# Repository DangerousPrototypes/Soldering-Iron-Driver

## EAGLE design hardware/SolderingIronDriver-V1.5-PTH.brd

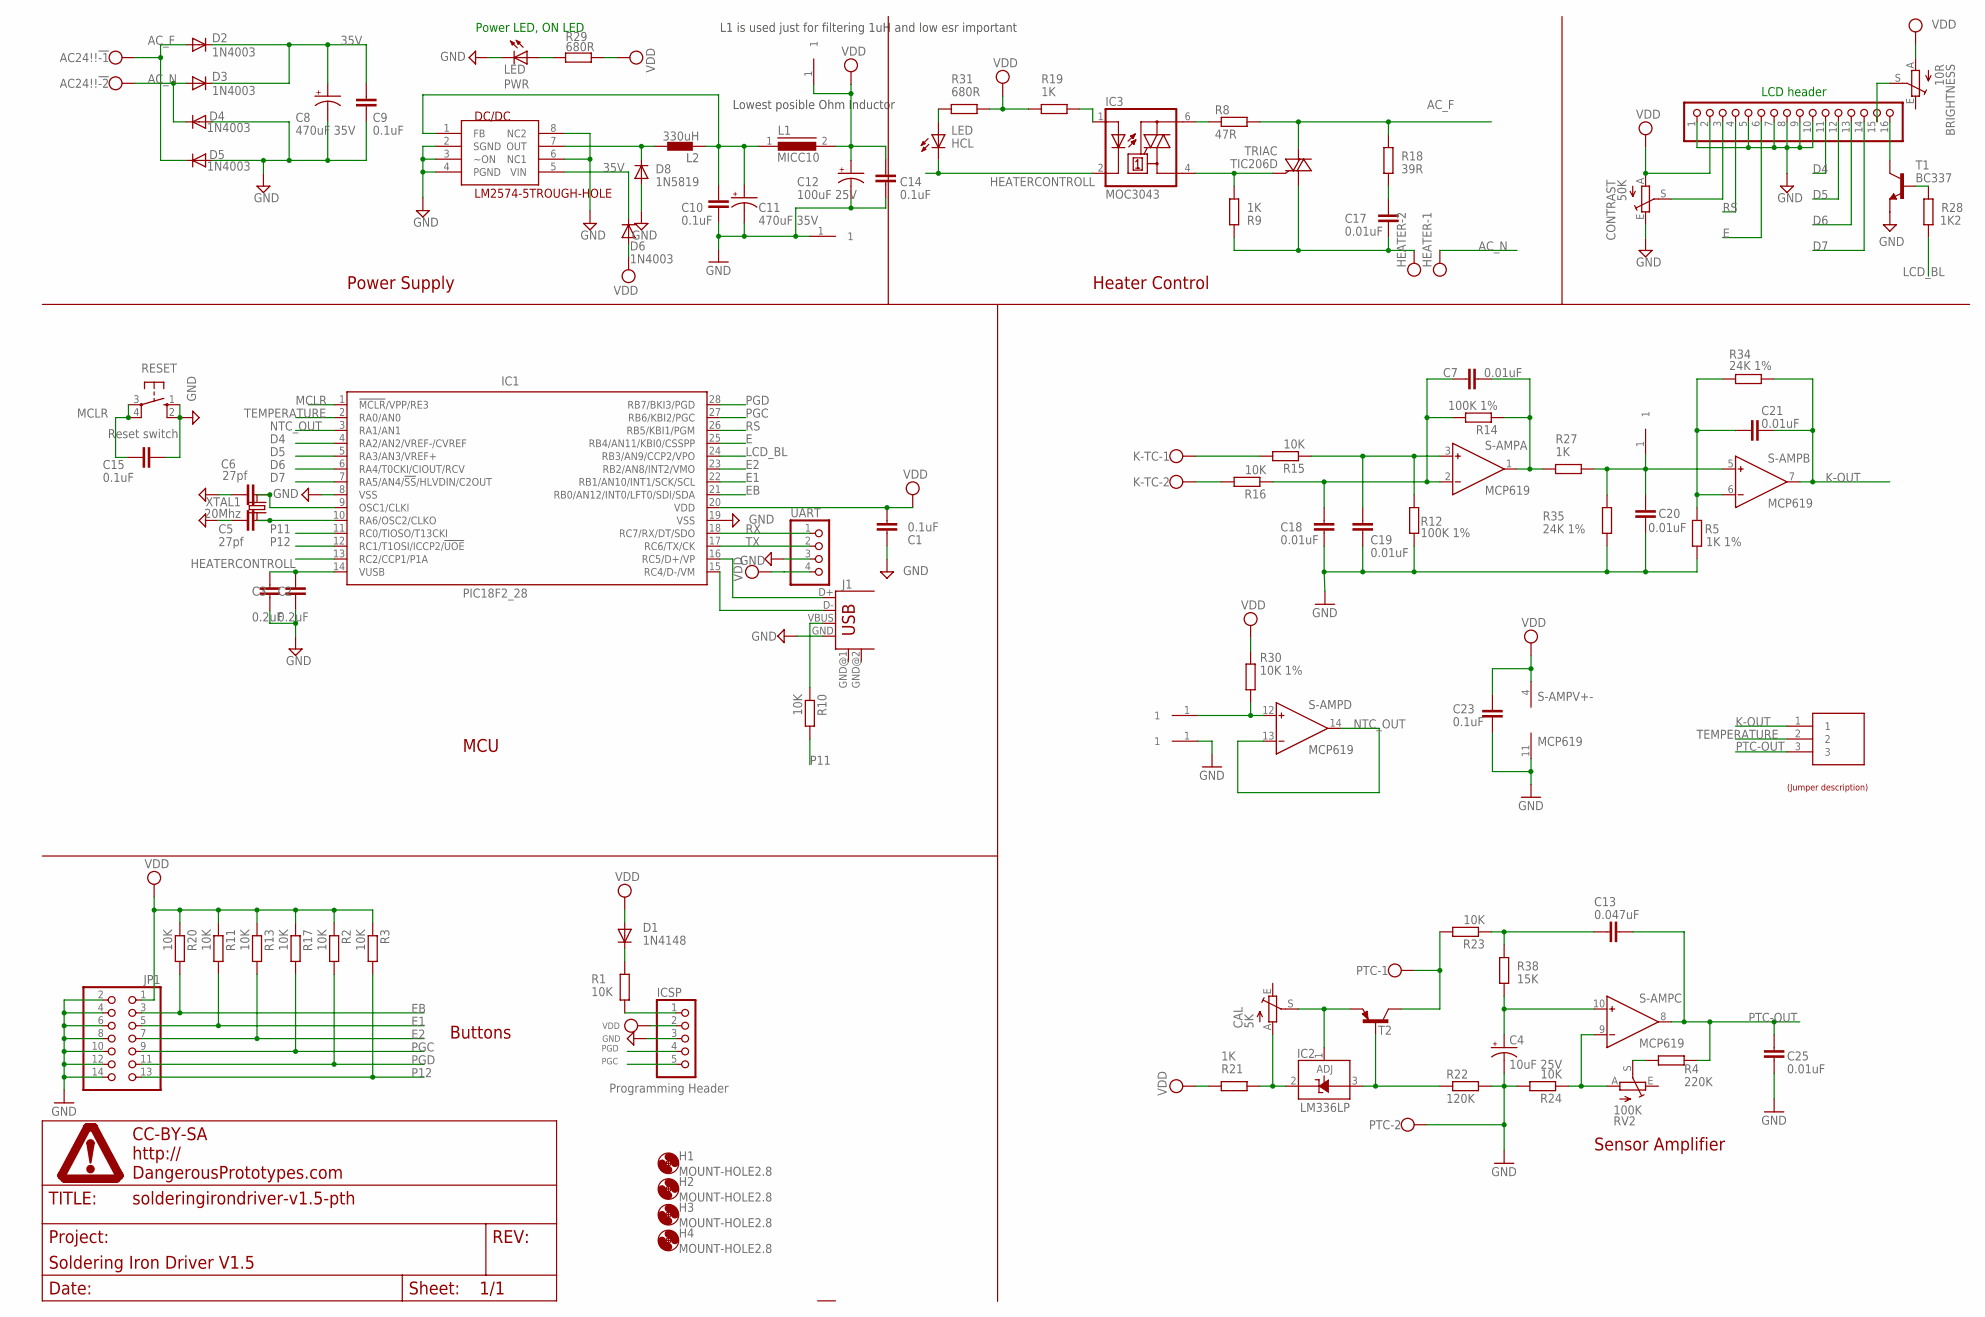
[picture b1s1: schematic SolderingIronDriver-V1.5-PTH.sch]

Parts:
5V: HEADER1X1PTH; M1X1
AC24!!!: W237-102
AMP: HEADER1X1PTH; M1X1
BRIGHTNESS: 10R; B25P
C1, C9, C10, C14, C15, C23: 0.1uF; DEC
C2, C3: 0.2uF; DEC
C4: 10uF 25V; CPOL-RADIAL-10UF-25V
C5, C6: 27pf; DEC
C7, C17, C18, C19, C20, C21, C25: 0.01uF; DEC
C8: 470uF 35V; CAP-D10-P200MIL
C11: 470uF 35V; CAP-D6.3MM-P100MIL
C12: 100uF 25V; CPOL-RADIAL-100UF-25V
C13: 0.047uF; DEC
CAL: 5K; RJ9W
CONTRAST: 50K; B25P
D1: 1N4148; DO35-7
D2, D3, D4, D5, D6: 1N4003; DO41-7.6
D8: 1N5819; DO41-7.6
DC/DC: LM2574-5TROUGH-HOLE; DIL-08
GND: HEADER1X1PTH; M1X1
H1, H2, H3, H4: MOUNT-HOLE2.8; 2,8
HCL: LED; LED3MM
HEATER: W237-102
IC1: PIC18F2_28; SOCKET-28-3
IC2: LM336LP; TO92
IC3: MOC3043; DIL06
ICSP: PINHD-1X5; 1X05
JP1: PINHD-2X7; 2X07
K-TC: W237-102
L1: MICC10
L2: 330uH; CW8A
LCD_HEADER: PINHD-1X16; 1X16
NTC: HEADER1X1PTH; M1X1
ON/OFF2: HEADER1X1PTH; M1X1
PTC: W237-102
PWR: LED; LED3MM
R1: 10K; 0204/7
R2, R3, R10, R11, R13, R15, R16, R17, R20, R23, R24: 10K; RTH025W
R4: 220K; RTH025W
R5: 1K 1%; RTH025W
R8: 47R; RTH025W
R9, R19, R21, R27: 1K; RTH025W
R12, R14: 100K 1%; RTH025W
R18: 39R; RTH025W
R22: 120K; RTH025W
R28: 1K2; RTH025W
R29, R31: 680R; RTH025W
R30: 10K 1%; RTH025W
R34, R35: 24K 1%; RTH025W
R38: 15K; RTH025W
RESET: 10-XX; B3F-10XX
RV2: 100K; RJ9W
S-AMP: MCP619; SOCKET-14
SENSOR_SELECT: HEADER1X3PTH; M1X3
T1: BC337; TO92-CBE
T2: BJT-PNPTO92EBC; TO92-EBC
TRIAC: TIC206D; TO220BV
U$1: DINA4_L; DP_LOGO
U$2: JUMP3_DESC
UART: PINHD-1X4; 1X04
USB: USB; USB-B-H
XTAL1: 20Mhz; HC49U70

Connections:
35V: C8.+, C9.2, D2.C, D3.C, D6.C, DC/DC.5 (VIN)
AC_F: AC24!!!.1, D2.A, D5.C, R8.2, R18.1, TRIAC.T2 (A2)
AC_N: AC24!!!.2, D3.A, D4.C, HEATER.1
D4: IC1.4 (RA2/AN2/VREF-/CVREF), LCD_HEADER.11
D5: IC1.5 (RA3/AN3/VREF+), LCD_HEADER.12
D6: IC1.6 (RA4/T0CKI/CIOUT/RCV), LCD_HEADER.13
D7: IC1.7 (RA5/AN4/!SS!/HLVDIN/C2OUT), LCD_HEADER.14
E: IC1.25 (RB4/AN11/KBI0/CSSPP), LCD_HEADER.6
E1: IC1.22 (RB1/AN10/INT1/SCK/SCL), JP1.5, R11.2
E2: IC1.23 (RB2/AN8/INT2/VMO), JP1.7, R13.2
EB: IC1.21 (RB0/AN12/INT0/LFT0/SDI/SDA), JP1.3, R20.2
GND: C1.2, C2.2, C3.2, C4.2 (-), C5.2, C6.2, C8.-, C9.1, C10.1, C11.-, C12.2 (-), C14.1, C15.1, C18.2, C19.2, C20.2, C23.1, C25.1, CONTRAST.E, D4.A, D5.A, D8.A, DC/DC.2 (SGND), DC/DC.3 (~ON), DC/DC.4 (PGND), DC/DC.6 (NC1), DC/DC.8 (NC2), GND.1, IC1.8 (VSS), IC1.19 (VSS), ICSP.3, JP1.2, JP1.4, JP1.6, JP1.8, JP1.10, JP1.12, JP1.14, LCD_HEADER.1, LCD_HEADER.5, LCD_HEADER.7, LCD_HEADER.8, LCD_HEADER.9, LCD_HEADER.10, ON/OFF2.1, PTC.2, PWR.K (C), R5.1, R12.1, R22.2, R24.2, R35.1, RESET.1 (S), RESET.2 (S1), S-AMP.11 (V-), T1.E, UART.3, USB.GND
HEATERCONTROLL: HCL.K (C), IC1.13 (RC2/CCP1/P1A), IC3.2 (C)
K-OUT: C21.2, R34.2, S-AMP.7 (OUT), SENSOR_SELECT.1
LCD_BL: IC1.24 (RB3/AN9/CCP2/VPO), R28.2
MCLR: C15.2, IC1.1 (!MCLR!/VPP/RE3), ICSP.1, R1.1, RESET.3, RESET.4 (P1)
unnamed: C6.1, IC1.9 (OSC1/CLKI), XTAL1.2
unnamed: C5.1, IC1.10 (RA6/OSC2/CLKO), XTAL1.1
unnamed: R10.1, USB.VBUS
unnamed: C10.2, C11.+, DC/DC.1 (FB), L1.1, L2.1
unnamed: R28.1, T1.B
unnamed: HCL.A, R31.1
unnamed: R4.2, RV2.S
unnamed: D1.C, R1.2
unnamed: LCD_HEADER.16, T1.C
unnamed: BRIGHTNESS.S, LCD_HEADER.15
unnamed: C2.1, C3.1, IC1.14 (VUSB)
unnamed: K-TC.1, R15.2
unnamed: CAL.S, IC2.1 (ADJ), T2.E
unnamed: C17.1, R18.2
unnamed: IC3.4 (A1), R9.1, TRIAC.G
unnamed: IC3.6 (A2), R8.1
unnamed: IC3.1 (A), R19.2
unnamed: C13.1, R23.1, R38.2
unnamed: NTC.1, R30.2, S-AMP.12 (IN+)
unnamed: K-TC.2, R16.2
unnamed: C7.1, C18.1, R14.2, R16.1, S-AMP.2 (IN-)
unnamed: C19.1, R12.2, R15.1, S-AMP.3 (IN+)
unnamed: C7.2, R14.1, R27.2, S-AMP.1 (OUT)
unnamed: IC2.3 (A), R22.1, T2.B
unnamed: CAL.A, IC2.2 (C), R21.1
unnamed: AMP.1, C20.1, R27.1, R35.2, S-AMP.5 (IN+)
unnamed: C21.1, R5.2, R34.1, S-AMP.6 (IN-)
unnamed: C4.1 (+), R38.1, S-AMP.10 (IN+)
unnamed: PTC.1, R23.2, T2.C
unnamed: R24.1, RV2.A, S-AMP.9 (IN-)
unnamed: PWR.A, R29.1
unnamed: CONTRAST.S, LCD_HEADER.3
NTC_OUT: IC1.3 (RA1/AN1), S-AMP.13 (IN-), S-AMP.14 (OUT)
P11: IC1.11 (RC0/TIOSO/T13CKI), R10.2
P12: IC1.12 (RC1/T1OSI/ICCP2/!UOE), JP1.13, R3.2
PGC: IC1.27 (RB6/KBI2/PGC), ICSP.5, JP1.9, R17.2
PGD: IC1.28 (RB7/BKI3/PGD), ICSP.4, JP1.11, R2.2
PTC-OUT: C13.2, C25.2, R4.1, S-AMP.8 (OUT), SENSOR_SELECT.3
RC4: IC1.15 (RC4/D-/VM), USB.D-
RC5: IC1.16 (RC5/D+/VP), USB.D+
RS: IC1.26 (RB5/KBI1/PGM), LCD_HEADER.4
RX: IC1.18 (RC7/RX/DT/SDO), UART.1
SW-OUT: D8.C, DC/DC.7 (OUT), L2.2
TEMPERATURE: IC1.2 (RA0/AN0), SENSOR_SELECT.2
TX: IC1.17 (RC6/TX/CK), UART.2
VDD: 5V.1, BRIGHTNESS.A, C1.1, C12.1 (+), C14.2, C23.2, CONTRAST.A, D1.A, D6.A, IC1.20 (VDD), ICSP.2, JP1.1, L1.2, LCD_HEADER.2, R2.1, R3.1, R11.1, R13.1, R17.1, R19.1, R20.1, R21.2, R29.2, R30.1, R31.2, S-AMP.4 (V+), UART.4
WHATEVER: C17.2, HEATER.2, R9.2, TRIAC.T1 (A1)

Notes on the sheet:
Programming Header
Reset switch
LCD header
Power LED, ON LED
Power Supply
Heater Control
Buttons
MCU
Sensor Amplifier
Lowest posible Ohm Inductor
L1 is used just for filtering 1uH and low esr important

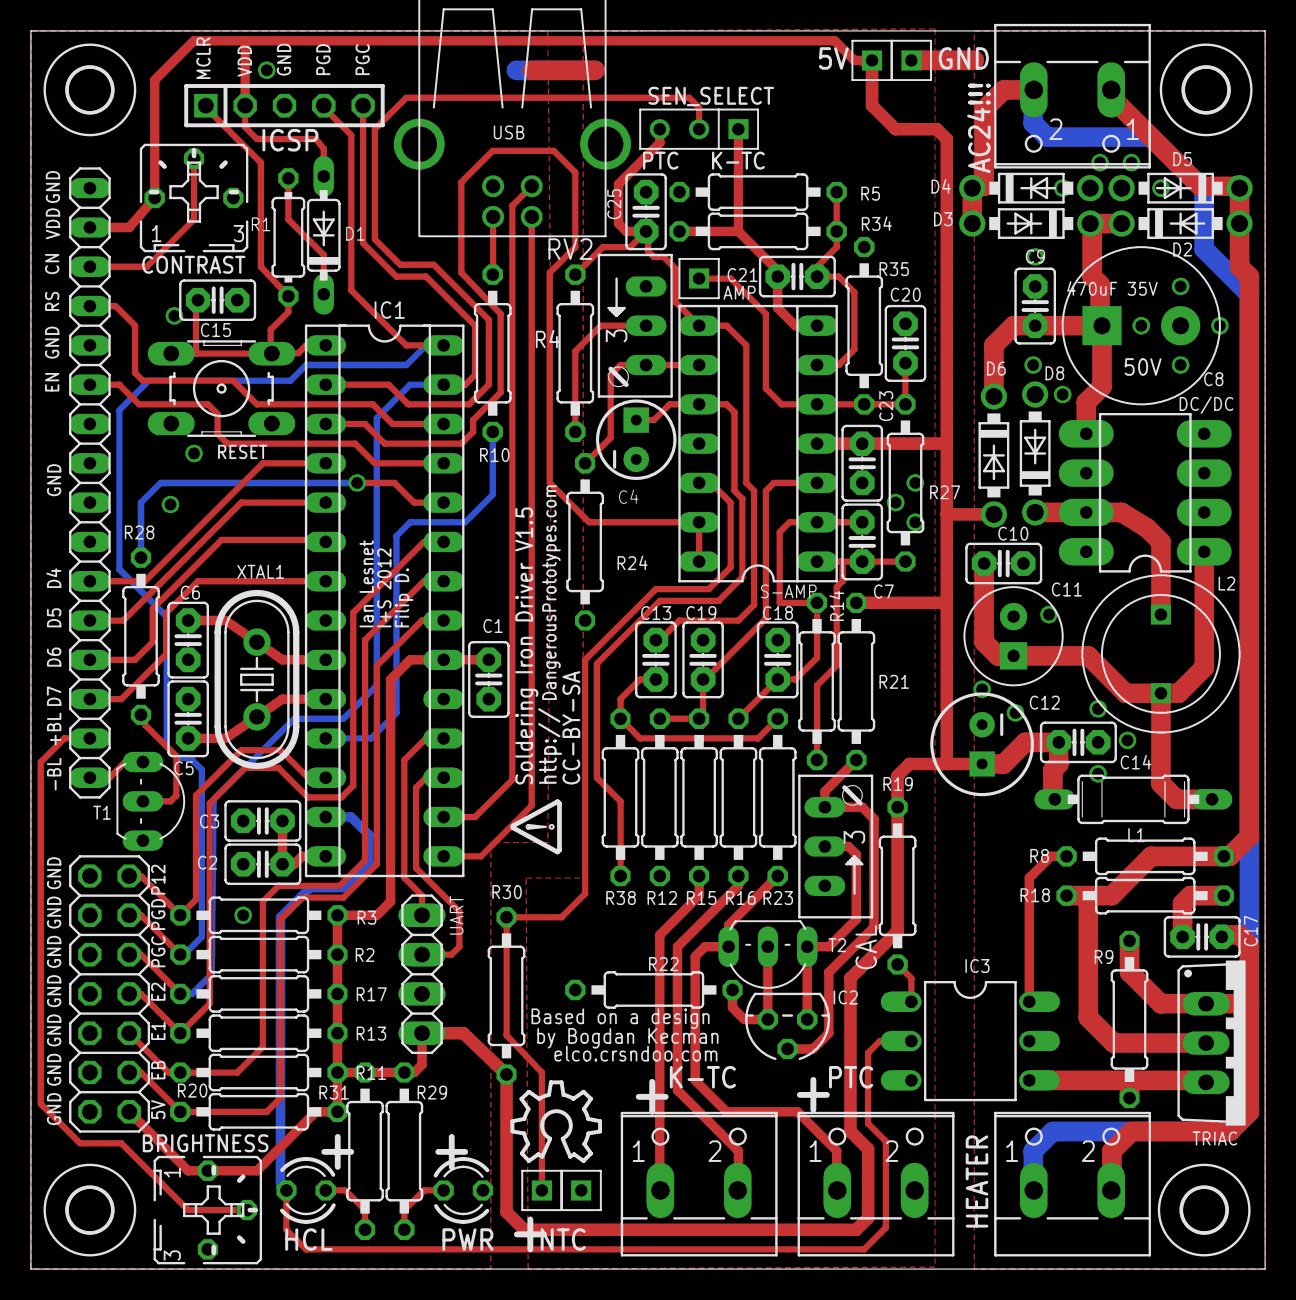
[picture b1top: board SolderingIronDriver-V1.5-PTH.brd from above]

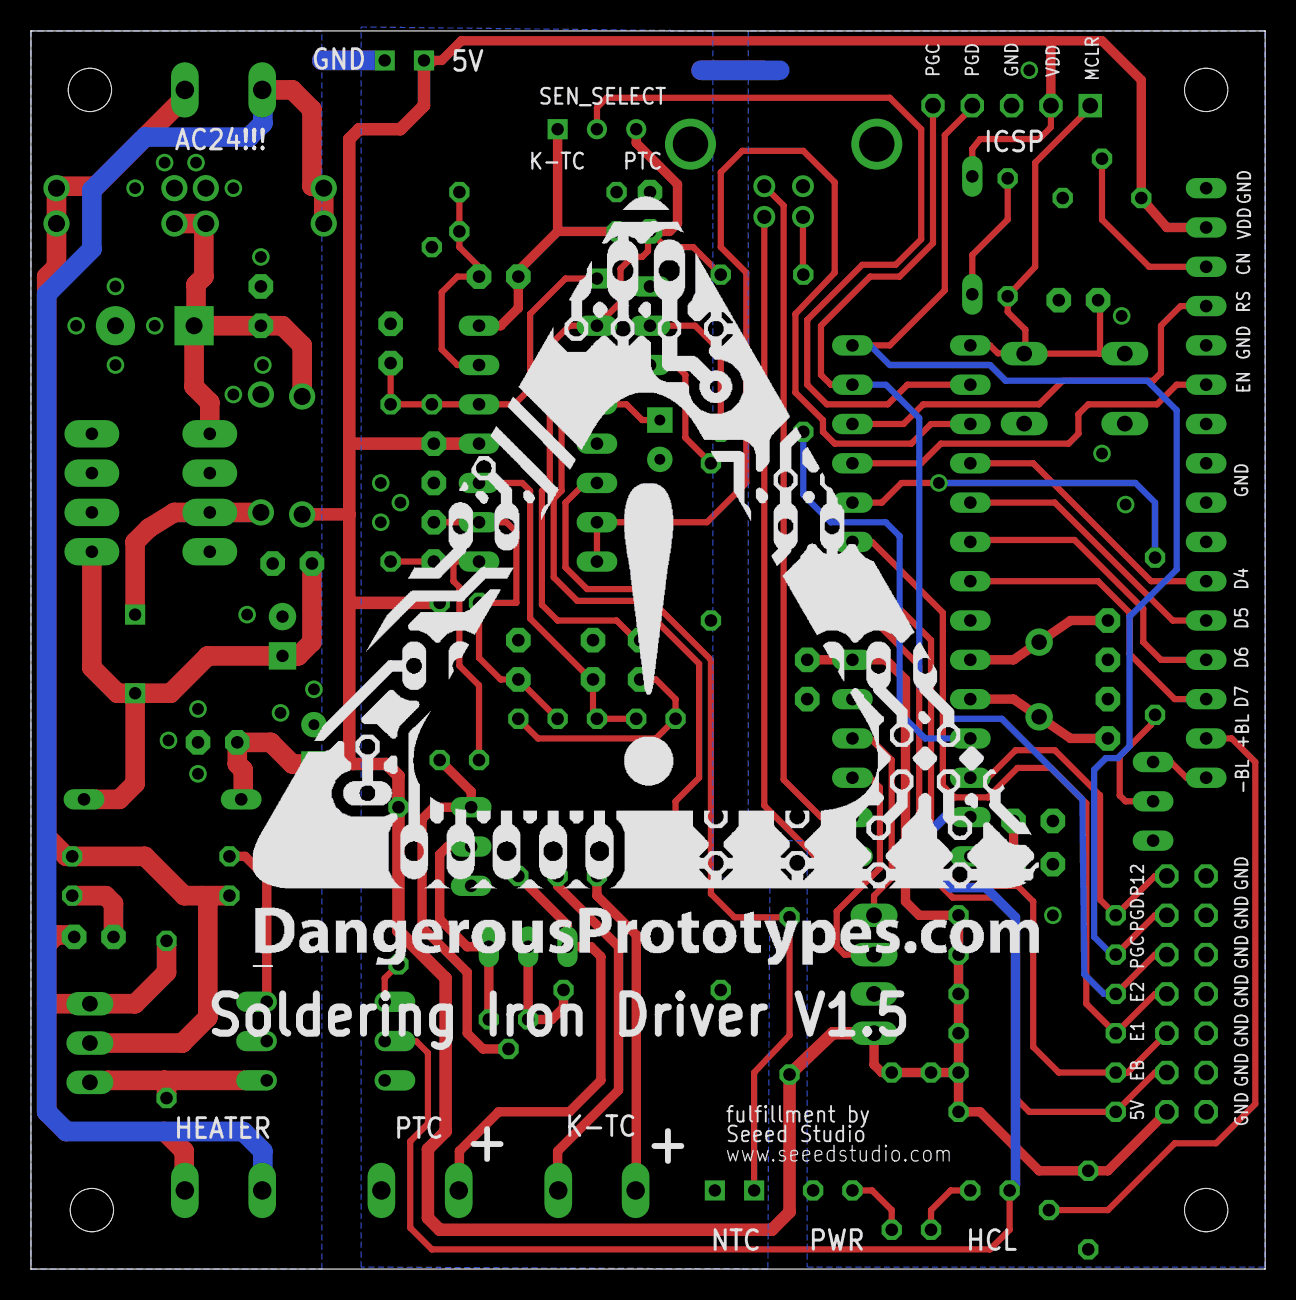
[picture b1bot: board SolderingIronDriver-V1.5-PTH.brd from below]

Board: 2 copper layers, 79.8 x 80.0 mm, 101 parts (2 on the bottom side), 63 nets.

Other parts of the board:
U$3: JUMP3_DESC
U$4: DP_LOGO_ART_2X2
U$5: OSHW_10X200_NOTEXT

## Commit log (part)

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2012-05-01 updated Bus Pirate v3.6 partlist
2012-05-01 Bus Pirate v3.6 manufacturing resources
2012-05-01 minor updates to the BP demobaord v5b
2012-05-02 renameing and small value changes to Bus Blaster v3.5, now V3b. also added new gerbers, partlist, and quote package. v3,5 removed
2012-05-02 Bus Blaster v3 JTAGkey buffer with self test
2012-05-02 Bus Blaster buffers
2012-05-02 Added integrated support of XSVF player for BPv4 only Added Windows side XSVF Player for BPv4 only (Built with Dev-C++) Has been based on previous specific BPv3 XSVF player (firmware-XSVFplayer)
2012-05-03 Added missing component values and preliminary partlist for the USB POV Toy v1c
2012-05-04 Bus Pirate firmware merged with JTR's 7 stack version. USB stack updated.
2012-05-04 Bus Pirate updates for v3 and v4 to work with JTR 7 stack update
2012-05-04 Bus Pirate v4 firmware update. fixed type in USB stack. Fixed include in project file.
2012-05-04 JTR 7 stack echo demo initial add
2012-05-04 Robots typo fix for the USB stack: http://dangerousprototypes.com/forum/viewtopic.php?f=39&t=3849&view=unread#unread
2012-05-04 JTR 7 stack echo demo minor spacing and comment updates
2012-05-04 Added USB echo demo for logic sniffer (18F24J50). Not working.
2012-05-08 New files for IR Toy with v.2a USB stack
2012-05-08 USB IR Toy merge with JTR stack
2012-05-08 Final IR Toy JTR stack update commit
2012-05-08 moved old POV Toy firmwares to attic
2012-05-08 Viswa's POV Toy firmware with USB stack integrated
2012-05-09 Added the Bus Pirate ADC demo project files,and archive
2012-05-09 Archive of the stack, and the exporte echo demo for the BP.
2012-05-11 Added 3306F type trimmer
2012-05-14 USB POV Toy v1c 3D model
2012-05-14 part ninja latest
2012-05-14 Added PEC12 model Incremental Encoder with switch. added pin marker on SSOP-20 footprint
2012-05-14 relocating misplaced images...
2012-05-16 Fix UART transparent mode for BPv4 and allow exit from tranparent mode with Normal button
2012-05-18 Added: 2x07 shrouded pin header
2012-05-24 removed base to collector resistor on T5, add base to emitter 10k resistor on T5, change value of resistors R16, R18, R19 to 10k, change value of resistor R15 to 1k, update trimmer to new footprint, 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
2012-05-24 upload image of schematic and board. upload gerber for v1c
2012-05-25 Added: FT230X, fix footprint of Tact switch and trimmer
2012-05-25 commit SSOP-16 footprint and updated FT230X part
2012-05-25 Part Ninja, firmware update: rehaul of the checkConduct function insted of using 5V---[r680]--ADC--[A][B]---GND....
    it's now 5V--[A][B]---[ADC]---[R680]----GND...
2012-05-28 Added: LM317 TO-220 vertical under VREG_3PINS_ADJ-* device. Renamed IC_VREG_3PINS devices to VREG_3PINS. Renamed IC_VREG_5PINS device to VREG_5PINS
2012-05-28 Part Ninja firmware updates: capacitor measurment testCap function (test.c) implemented through comparator interrupt in main.c
2012-05-28 Part Ninja firmware:
    made updates to testCap function in test.c,
    it now brings the untested 3rd bin low, to keep it from accidentally causing a comparator interrupt, if the unused comparator is connected to it...
2012-05-29 Part Ninja with usb debuging...
2012-05-30 Part Ninja, some minor changes to functions...
2012-05-30 part ninja hex
2012-05-30 Fix FT230X SSOP-16 footprint, added SSOP-16-FTDI footprint
2012-05-30 Bus Blaster test buffer minor updates, added v4 UCF from Skot9000: http://dangerousprototypes.com/forum/posting.php?mode=reply&f=37&t=3503#pr39413
2012-05-31 simpple fix in main.c
2012-05-31 Added the Part name in the processing app, also added pinout to th ePN firmwarem and app, as well as a hex
2012-05-31 Part Ninja, fixed Triac function....minor adjustments to the processing app.
2012-05-31 Part Ninja firmware update with cdc controll functions, and processing app updated with the same controll functions
2012-05-31 Part ninja processing app with cross platform exe files... the app displays the available com ports, once you clik on the one the part ninja is connected to it starts copying the debug info into the 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
2012-06-01 Part ninja Processing app updates, and minor changes to the PN source...
    teh Proc update now functions from the executable exe files as welll
2012-06-01 moved and updated artwork
2012-06-04 SPIsniffer app Speed fix for some PCs on serial port initialization: http://dangerousprototypes.com/forum/viewtopic.php?f=4&t=4109&view=unread#p41202
2012-06-04 small changes to the processing app, added sugest part Button
2012-06-04 cleaded upp the app some/processing Part Ninja
2012-06-04 3D model, and artwrork for the pic32Dip
2012-06-05 Misc files found during housekeeping
2012-06-05 Part ninja minor fix
2012-06-05 processing app updates
2012-06-05 Part Ninja firmware: PN now ignores unrecognised commands
2012-06-08 update Bus pirate v3.6 to v3.6a. Fix IO shrouded header 2x05 to correct silk length.
2012-06-08 Part Ninja firmware, and app darlington upgrade, added pics for the sch a,d brd files of the ATX psu v1.1, and BP v3.6
2012-06-11 USB IR Toy v3 3d model and rendered images
2012-06-12 bus pirate binmode SPI speed fix from: http://dangerousprototypes.com/forum/viewtopic.php?f=40&t=3864#p38949
2012-06-13 Bus Pirate ADC2UART demo code
2012-06-14 Part Ninja - tests- part recognition diagrams
2012-06-15 USB echo demo ported to the PIC18F2550 Breakout Board
2012-06-15 PIC24FJGB002 Breakou Board USB echo demo ported
2012-06-20 Drg drop Bus Pirate update from: http://dangerousprototypes.com/forum/viewtopic.php?f=4&t=4194&view=unread#p41685
2012-06-25 Added devices: 74HC4017 (TSSOP16), 74HC595(TSSOP16), ULN2003(TSSOP16) and 555 (SOIC8)
2012-06-25 atx sales page
2012-06-27 USB descriptor and PID fix ( http://dangerousprototypes.com/track/view.php?id=39 bug fix)
2012-06-29 Device identification AVRISP_2 changed to STK500_2 to make it work with AVR STUDIO 5 and above .
    In avrdude, set programmer as STK500V2 .
2012-06-29 1.POVTOY_DISPLAY_FRAME_DELAY symbol to specify start delay in both direction. 2.Some fine tuning
2012-07-02 ATX BB render and model
2012-07-10 renaming scheme, and added 3d models and laser cut files for the ATXv1.1 SoB case
2012-07-11 *3d models and SVG files for the ATX cases
2012-07-12 updated atx psu v1.1 to v1.2, fix the swapped labels of R2 and D2
2012-07-13 baseIO.c : UART1RXRdy() define is converted to function to be consistent with BPv4. This also fixes compilation error in BPv3 due to changes in previous revision.
    Workspaces, translation etc.. : File names renamed with BPv3 and BPv4 prefixes consistency.
2012-07-13 base.h : translation files have BPv3 or BPv4 prefix
2012-07-13 update board to v1d, fix "Fulfillment" spelling
2012-07-16 BP LCD v3a 3d model and render
2012-07-17 ATX BB SoB v1 manuf resources update...also xls quote added
2012-07-17 add the SU templates folder with Sketchup source files for the varius templates standard sizes
2012-07-17 added guidelines to the 6037 template Su
2012-07-19 Commit Bus Blaster v4.1 brd, a Bus Blaster v4 fitted to Standard DP9056 PCB
2012-07-23 updated v3 and v4 shrouded header with the correct silk, fix v4 "Fufillment" mispelling. Please use latest v3c and v4.1a
2012-07-23 Bus Blaster v3c 3d model and rendering
2012-07-24 Added parts: KSZ8851SNL, TPS6120X, 2X08 HEADER, 3x6 mm 2pins switch, 1.8" TFT LCD Added 2x10 Shrouded Pin Header variant to existing 2x10 Header
2012-07-25 Bus Blaster v3 svg files, and BoM
2012-07-25 Exploaded sob case assemplby 3d model
2012-07-25 Update for BP v4 Passive LCD adapter v1a -renamed to BPv4LCDadapter v1b -added 74HC595 serial to parallel -removed polarity jumpers? (2x03) of LCD backlight -added control transistor of the backlight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
2012-08-08 Added 74AC573 in SOIC-20 changed Oscillator prefix to 'X'
2012-08-09 Added: FT311D in LQFP-32
2012-08-13 ATX 1.1 SoB v1 model and renderings
2012-08-14 Changes to USB interrupt from JTR
2012-08-14 Added USB interrupt fix to BPv4 from: http://dangerousprototypes.com/forum/viewtopic.php?f=28&t=3441&start=45#p42038
2012-08-14 UART inverse transmit pin was omitted in all BP versions:
    http://dangerousprototypes.com/track/view.php?id=47
2012-08-16 Bus Pirate Demo board firmware
2012-08-20 Added device: 23LC1024 SRAM in SOIC-8
2012-08-27 update to blog theme with header fix, switch for contest theme.
2012-08-27 blog theme contest template update
2012-08-27 update ATX PSU v1.2: expanded ATX Connector drill pads from 1.4mm to 1.7mm, "Fulfillment" spelling fixed
2012-09-04 revised credit card sized PCB based on ISO.IEC 7810 ID-1 identification cards sizes, size changed from 85 x 56 mm to 85.60 x 53.98 mm
2012-09-04 update Standard rectangular PCBs devices
2012-09-05 SU originals for the ATX case laser cutting
2012-09-06 little file reshuffeling in the ATX laser cutt files
2012-09-07 Fix IN-12 socket, replaced with correct cutout.
2012-09-07 Added: IN-12 Nixie tube display, IN-12 Socket cutout footprint Fixed: IN-12 Socket
2012-09-10 Sick of beige generic model, and render images
2012-09-12 first commit of DP KiCAD part library
2012-09-12 DP KiCAD parts
2012-09-13 .lib and .mod files converted using eagle2kicad-0.d.ulp from http://www.modulbot.com/download.html Fixed undefined DRAW command when loading to symbol library to KiCAD
2012-09-17 add bus pirate v5c board, enlarge ADC Input label
2012-09-20 Bus Pirate v4 Sick of Beige case laser cutting files and partlist(BOM)
2012-09-21 SoB case generator plugin from Tayken
2012-09-24 maker faire new york banner
2012-09-24 Added new Logic shrimp v2b, this version uses 23LC1024 SRAM
2012-09-25 added direction info on birectional buffer ICs
2012-09-25 initial Smoke Tester project folder
2012-09-25 Board files
2012-09-26 swapped drain and source pin of the p-mosfet controlling fuse blown switch
2012-09-27 OHS 2012 presentations
2012-10-01 Smoke Tester 3D model and renders
2012-10-02 Added MIC2027, D8035E VFD and update Arduino outline header placement outline
2012-10-07 adding an assortment of 3d models. They should all have origins centered properly about the pins. These were not checked thoroughly, but do appear to be generally correct. Most models are tweaked fro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
    The QFN32 is original and should be extremely easy to scale and accommodate other numbers of pins.
2012-10-08 Added: TD62783 8 Ch high side voltage source driver Updated: 74595 shift register symbol, changed pin names of SCLK, SDA, LATCH and RST
2012-10-08 Added: D8035E VFD board, composed of 3 boards. Board A, B and C
2012-10-08 VFD Board, render and 3D model..
2012-10-09 added series diode on Vusb in and Vin header, moved C8 beside SD holder
2012-10-10 first cut at molex KK series connectors. The 1x2 should be modeled in such a way that it's side stackable, so it will be easy to make additional even numbered connectors. These were based on a model 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
    These should be "close enough" for most purposes, alignment appears to be off a bit on the 4pos header though.
2012-10-10 ATO fuse clip, ATO fuse holder, and ATO jumper. Created from a minimal datasheet from Littlefuse 01000057Z.
    Can be found at Mouser:
    http://www.mouser.com/ProductDetail/Littelfuse/01000057Z/?qs=sGAEpiMZZMtN62bhLohzxVzkiLrmT5C%2f
    Other alternatives for high current voltage selection were discussed here:
    http://dangerousprototypes.com/forum/viewtopic.php?f=56&t=4509
2012-10-10 Added: 3D models for 2 trough-hole IC and a metalized Capacitor.
2012-10-10 Added SF303GJ26-3 JOYSTICK
2012-10-11 added version 2
2012-10-18 adding some 3.5mm side stacking screw terminals. The model is based on a phoenix 1984617, but should be representative of most side-stacking 3.5mm screw terminals.
    An individual component is also included, which should makes it really easy to quickly generate any number of positions (just do a move/copy, explode the components, and erase the lines along the sea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
2012-10-18 correcting the naming for the 2512 resistor model
2012-10-18 adding a 2010 resistor
2012-10-18 Added device: MicrosSD fold type socket, PIC24F16KA102, 1x2 SMD solder jumper. fix Arduino 1x8 header containing pin 8 - 13, offset ed location.
2012-10-18 Bus blaster v3 v4 manufacturing resrouces
2012-10-19 fix PIC24F16KA102 vector text overlap on its symbol Add SOIC-14 package on PIC16F1823
